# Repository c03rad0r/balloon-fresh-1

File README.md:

# Pico-Balloon Tracker & E80 Range Test Bench

**A pico-balloon relay system: balloons acting as a bent pipe between base stations.**

A flight hub carries a 2.4 GHz FLRC radio, GNSS and a solar harvester, and carries four solar wings. Two
ground base stations reach each other **only through the balloon** — there is no ground-to-ground path.
Each base station has cellular backhaul — LTE Cat 4 (SIM7600E-H), not 5G. See
`docs/TELCO-BACKHAUL-DECISIONS.md` R3: "LTE Cat-4 now. Do NOT buy 5G."

**This README has two parts.** The relay system (below) is the current programme. The E80-STM32 range
test bench further down is the bench instrumentation used to characterise the radio link.

---

## 💬 Discussion & community

Questions, design review and build reports are welcome in the **Pico-Balloon Signal group**:

**https://signal.group/#CJQKIPXPvMIsyJiDb-IwW7FDIM21SUhsRrSs1VqZI30MCaenEhDGbhyyJSvjaXNYMcUDeXGj**

Signal is used deliberately: it needs only a phone number (no email, no account to create) and the
group is end-to-end encrypted, which suits a hardware project where measurements and part choices get
discussed before anything is public. If the invite link has expired, open an issue and ask for a
fresh one.

*New here?* The honest current state of the board — what works, what is open, and what is explicitly
not yet done — is in the **⚠️ Honest state** section just below. Please read it before asking
"is it ready to fly?", because the answer there is kept current and this README is the canonical
place for it.

---

## 🛰 The relay system

### Board status

**Generated** — `docs/boards/GALLERY.md` has renders and a measured table. Regenerate with
`python3 tracker/hardware/make_board_gallery.py`.

| board | footprints | nets routed | tracks | what it is |
|---|---|---|---|---|
| **hub v9** | 59 | **57 / 59** | 834 | flight hub: SX1280 FLRC, GNSS, solar harvester, 4 wing sockets |
| **wing v9** | 15 | **4 / 6** | 20 | wing solar array + cut driver + hub tab |
| **base station** | 44 | **0 / 44** | 0 | ground: SIM7600E-H LTE Cat 4, FLRC to the hub |

Read the `nets routed` column, **not** the amount of copper in a render — a copper pour is not routing.

### Start here by goal

| I want to… | read |
|---|---|
| see the fabrication questions we are asking a fab | [`docs/fab/JLC-QUERY-DRAFT-MESSAGE.md`](docs/fab/JLC-QUERY-DRAFT-MESSAGE.md) |
| see the fab-review reading order | [`docs/fab/README.md`](docs/fab/README.md) |
| see where every gate stands | [`docs/fab/GATE-RESULTS.md`](docs/fab/GATE-RESULTS.md) |
| see what is still missing | [`docs/fab/ASTRA-GAP-ANALYSIS.md`](docs/fab/ASTRA-GAP-ANALYSIS.md) |
| see per-board renders + measured state | [`docs/boards/GALLERY.md`](docs/boards/GALLERY.md) |
| read the wing interface decision record | [`docs/adr/046-wing-board-interface.md`](docs/adr/046-wing-board-interface.md) |

### ⚠️ Honest state

**Fit to show a fabricator for review. Not fit to order.** Open items:

- **`U1.41`** — the radio's exposed ground pad ~~**has no net** (pad-number mismatch)~~ — **CORRECTED
  2026-10-17:** measured, `U1`'s 13 pads numbered `41` are **all on `GND`** (thermal-via array, correct
  by design) and its 9 unnamed pads are `F.Paste`-only stencil apertures. Not a defect. Owning record:
  [`docs/fab/U1-FOOTPRINT-DIAGNOSIS.md`](docs/fab/U1-FOOTPRINT-DIAGNOSIS.md)
- **ERC: 20 errors** — incl. 12 floating `U_CUT1–4` pins; **parity passes**, so the board has not drifted
- **DRC: 16 errors — all 16 are the intentional `J_W*` edge lands. Zero real electrical errors.** The 137
  warnings are silkscreen or library metadata
- **Wing joint geometry is OPEN** (ADR-046 §4.2.1) — so the interface drawing is **held**
- **Base station: 0 of 44 nets routed**, no editable schematic

### Generate the artefacts

```bash
python3 tracker/hardware/make_board_gallery.py      # renders + the measured table
python3 tracker/hardware/make_system_diagram.py     # the diagram above
bash    tracker/hardware/run_erc.sh                 # ERC + schematic-to-board parity
bash    tracker/hardware/fab_grade.sh tracker/hardware/hub_board_v9.kicad_pcb tracker/hardware/output/fabgrade
~/venvs/kicad/bin/python tracker/hardware/tests/test_netlist_integrity.py
```

All three gates are recorded in [`docs/fab/GATE-RESULTS.md`](docs/fab/GATE-RESULTS.md).

### Visual review — how artefacts are checked here

A visual consultant (`gpt-6-astra`) reviews every generated diagram before it is committed:

```bash
python3 tracker/hardware/ask_astra.py --review artefact.png --out review.md
```

**This is not decoration.** It has caught two architecture errors in the system diagram alone — a
one-base-station topology that could not depict a relay, and a wiring path that drew the direct
ground-to-ground link its own label denied. Both survived reading the generator code. See
[`docs/fab/reviews/`](docs/fab/reviews/).

**Regenerate before reviewing.** Reviewing a stale render is reviewing a file that no longer exists.

---

## 🧪 E80-STM32 range test bench

Ultralight (<15 g) pico-balloon tracker (ESP32-C3 + Semtech LR2021) with a
dedicated **E80-STM32 bench firmware** for distributed LoRa/FLRC range
testing.  Two boards, two laptops, one `make` command each — that's all
it takes to run a full PER / RSSI / SNR sweep.

---

## ⚡ Getting Started

```bash
git clone https://github.com/felixfelix-bot/balloon-fresh.git
cd balloon-fresh/firmware/e80-stm32-bench
git checkout feat/2g4-sweep

# One-time: flash the board (needs both USB cables connected)
make flash

# On the TX machine:
make tx

# On the RX machine (within 4 minutes of `make tx`):
make rx

# After both finish, merge logs:
make range-merge RX=rx-log.csv TX=tx-log.csv
```

**That's it.** The system auto-detects serial ports, computes a synchronised
start time (T0), beeps a countdown, and writes results to CSV.

> **Want the minimal package?** Download the pre-built
> [range-test ZIP](../../releases) — contains only the files you need to
> flash + run TX/RX. See [Part 4](#4-minimal-range-test-zip) below.

---

## 📋 Table of Contents

| # | Section |
|---|---------|
| 1 | [What is this repo?](#1-what-is-this-repo) |
| 2 | [Hardware Requirements](#2-hardware-requirements) |
| 3 | [Quick Start (Linux / macOS / Windows)](#3-quick-start) |
| 4 | [Minimal Range-Test ZIP](#4-minimal-range-test-zip) |
| 5 | [Repository Structure](#5-repository-structure) |
| 6 | [Key Documentation](#6-key-documentation) |
| 7 | [Tools Reference](#7-tools-reference) |
| 8 | [Config Presets](#8-config-presets) |
| 9 | [Development & Testing](#9-development--testing) |
| 10 | [Hardware](#10-hardware) |

---

## 1. What is this repo?

This repository hosts **two related projects**:

1. **Pico-Balloon Tracker** — An ESP32-C3 + Semtech LR2021 ultra-light
   balloon tracker (<15 g) with multi-band LoRa (2.4 GHz + Sub-GHz), FLRC
   high-speed mode, 3D PCB-Yagi antenna array, solar/supercap power, and
   BMP280 sensing.

2. **E80 Range Test Bench** — A STM32F103C8T6 based firmware (`firmware/e80-stm32-bench/`)
   for the E80-900MBL-02 board, used for distributed LoRa/FLRC range
   testing.  Measures PER, RSSI, SNR, and bit error rate across modulation
   schemes at various distances.  Two boards act as TX/RX, each connected
   to a separate computer.  Role is set at runtime — boards are
   interchangeable.

---

## 2. Hardware Requirements

| Item | Qty | Notes |
|------|-----|-------|
| E80-900MBL-02 board | 2 | One per machine. Boards are interchangeable (TX/RX is software-selected). |
| Computer (laptop/mini PC) | 2 | One per board. Linux, macOS, or Windows. |
| USB cables | 2 per board | CH340 USB-serial (data) + CMSIS-DAP/Pico SWD probe (debug). Both required. |
| Phone with GPS | 1 (opt.) | For distance measurement. Any app that exports GPX/KML. |

### E80 Board Anatomy

- **STM32F103C8** — microcontroller (64 KB flash / 20 KB RAM)
- **LR2021** — Semtech LoRa Gen 4 radio (supports LoRa + FLRC)
- **CH340** — USB-serial chip for host communication
- **Raspberry Pi Pico** (CMSIS-DAP) — SWD probe for flashing + board reset

### Pico-Balloon Hardware

| Component | Spec |
|-----------|------|
| MCU | ESP32-C3 (ESP-C3-12F / XIAO ESP32C3) |
| LoRa | Semtech LR2021 (Gen 4) / LR1121 (Gen 3 alt.) |
| PA/LNA | Skyworks SKY66112-11 (+22 dBm TX, +14 dB LNA RX) |
| Antennas | 4× PCB-Yagi + SP4T switch (lighthouse mode) |
| Power | 12× solar cells → BAT54 → 2× 3.3 F supercaps → TPS7A02 LDO |
| Sensor | BMP280 (pressure/temperature) |
| Target weight | <15 g |

---

## 3. Quick Start

### Linux

```bash
# Install toolchain
sudo apt install cmake arm-none-eabi-gcc openocd python3 python3-pip
pip install pyserial

# Clone & build
git clone https://github.com/felixfelix-bot/balloon-fresh.git
cd balloon-fresh/firmware/e80-stm32-bench
git checkout feat/2g4-sweep

# Add user to dialout group (needed for serial port access)
sudo usermod -aG dialout "$USER"
# Log out and back in, or: newgrp dialout

# Flash firmware (first time only — both USB cables connected)
make flash
```

### macOS

```bash
# Install toolchain
brew install cmake gcc-arm-embedded openocd python3
pip3 install pyserial

# Clone & build
git clone https://github.com/felixfelix-bot/balloon-fresh.git
cd balloon-fresh/firmware/e80-stm32-bench
git checkout feat/2g4-sweep

make flash
```

### Windows

1. Install [STM32CubeIDE](https://www.st.com/en/development-tools/stm32cubeide.html)
   or a standalone `arm-none-eabi-gcc` toolchain.
2. Install [OpenOCD](https://gnutoolchains.com/arm-eabi/openocd/).
3. Install [Python 3](https://www.python.org/downloads/) + `pip install pyserial`.
4. Clone the repo, open a terminal (Git Bash or PowerShell) in
   `firmware/e80-stm32-bench/`.
5. Run `make flash`.

### Running a Test

```bash
# On TX machine:
make tx

# On RX machine (within 4 minutes of make tx):
make rx

# After both finish (either machine):
make range-merge RX=rx-log.csv TX=tx-log.csv
```

> For full instructions including flashing details, serial port detection,
> GPS stitching, and troubleshooting, see the
> **[E80 Range Test Operator Guide](firmware/e80-stm32-bench/docs/RANGE-TEST-GUIDE.md)**.

---

## 4. Minimal Range-Test ZIP

For operators who just want the files needed to flash + run TX/RX without
cloning the whole repo:

**Download:** See [GitHub Releases](../../releases) for `e80-range-test-*.zip`.

**Build your own:**

```bash
cd firmware/e80-stm32-bench
bash tools/create-range-test-zip.sh
# Output: e80-range-test-<sha7>.zip
```

The ZIP contains:

| Path | Description |
|------|-------------|
| `Makefile` | Convenience targets (flash, tx, rx, merge) |
| `CMakeLists.txt` | Firmware build config |
| `cmake/` | Toolchain file (arm-none-eabi) |
| `ld/` | Linker scripts (STM32F103C8) |
| `src/` | Firmware source code |
| `third_party/` | STM32 HAL + Semtech LR2021 driver |
| `tools/e80_bench_ctl.py` | Board controller — TX/RX, PER bench |
| `tools/e80_detect.py` | Auto-detect board serial port |
| `tools/gps_stitch.py` | Stitch GPS track onto RX packet log |
| `tools/merge_csvs.py` | Merge TX + RX logs into PER report |
| `tools/countdown.py` | Countdown timer with beeps |
| `configs/envelope-4cfg-max.json` | Default range test preset (4 configs, max payload) |
| `configs/outdoor-10.json` | Outdoor range test preset (10 pkts per config) |
| `docs/RANGE-TEST-GUIDE.md` | Full operator guide |
| `README-RANGE-TEST.txt` | Quick start card |

---

## 5. Repository Structure

```
balloon-fresh/
├── firmware/
│   ├── e80-stm32-bench/          # E80 STM32 range test firmware
│   │   ├── Makefile              # Flash, tx, rx, merge targets
│   │   ├── CMakeLists.txt        # Firmware build config
│   │   ├── src/                  # Firmware source (bench, radio, console)
│   │   ├── tools/                # Python tools (comms, GPS, CSV, sweep)
│   │   ├── cmake/                # ARM cross-compile toolchain
│   │   ├── ld/                   # STM32 linker scripts
│   │   ├── third_party/          # STM32 HAL + Semtech LR2021 driver
│   │   ├── docs/                 # RANGE-TEST-GUIDE, flashing, timing analysis
│   │   ├── tests/                # Host-side unit tests (C unit + pytest)
│   │   └── FLASHING.md           # Flashing procedures
│   ├── esp32-c3-flrc/            # ESP32-C3 FLRC bench firmware
│   ├── esp32-bootsel-controller/ # ESP32 boot/select controller
│   ├── esp32-uart-bridge/        # UART bridge firmware
│   ├── rp2040-flrc-max/          # RP2040 FLRC tests
│   └── scripts/                  # Build/deploy scripts
├── mesh-stack/                   # ESP-NOW mesh + FLRC bench + LR2021 drivers
├── hardware/                     # PCB design (KiCad), enclosures
├── configs/                      # Range test config presets (JSON)
├── tools/                        # Shared repo-wide tools & scripts
├── docs/                         # Project documentation, ADRs, plans
├── data/                         # Captured test data & analysis
├── tests/                        # Integration tests
├── bom/                          # Bill of materials
├── ansible/                      # Deployment playbooks (range-setup)
├── scripts/                      # Repo-wide automation scripts
└── tracker/                      # Ground station & tracker firmware
```

---

## 6. Key Documentation

| Document | Description |
|----------|-------------|
| **[Harmonized Cross-Board Bench Package](docs/harmonized/HARMONIZED-BENCH-PACKAGE.md)** | Entry point for cross-board (E80 / ESP32 / RP2040) bench work — real repo URLs and branches, build/flash per family, running a session, handing data back |
| [Harmonized Results](docs/harmonized/HARMONIZED-RESULTS.md) | Results summary by board-pair × band × LEN × BR, with raw CSV links; 868 MHz baseline vs 2.4 GHz semantics |
| [Harmonized Run Report Template](docs/harmonized/HARMONIZED-RUN-REPORT-TEMPLATE.md) | Fill-in template for one harmonized run (identity, provenance, matrix, acceptance, results, anomalies) |
| [Bench Console Spec](docs/BENCH-CONSOLE-SPEC.md) | Normative cross-board console protocol (`ID?/SET/N/PKT/STAT?`, framing, bands) |
| **[E80 Range Test Guide](firmware/e80-stm32-bench/docs/RANGE-TEST-GUIDE.md)** | Complete self-contained operator guide — hardware setup, flashing, TX/RX, merge, GPS, troubleshooting |
| [E80 Flashing Guide](firmware/e80-stm32-bench/FLASHING.md) | Detailed flashing procedures (SWD, stm32flash) |
| [Timing Tolerance Analysis](firmware/e80-stm32-bench/docs/timing-tolerance-analysis.md) | T0 sync mechanism analysis |
| [Hardware Integration Findings](firmware/e80-stm32-bench/docs/hardware-integration-findings.md) | Live hardware test results |
| [Operator Quickstart](firmware/e80-stm32-bench/tools/OPERATOR-QUICKSTART.md) | Quick reference for command structure |
| [ADR Index](docs/adr/) | Architecture Decision Records |
| [Hardware Connections](docs/hardware/HARDWARE_CONNECTIONS.md) | Board wiring reference |

---

## 7. Tools Reference

| Tool | Location | Purpose |
|------|----------|---------|
| `e80_bench_ctl.py` | `firmware/e80-stm32-bench/tools/` | Main board controller — TX burst, RX arm, PER measurement, sweep runner |
| `e80_detect.py` | `firmware/e80-stm32-bench/tools/` | Auto-detect E80 board role + serial port (handles CH340 port swapping) |
| `gps_stitch.py` | `firmware/e80-stm32-bench/tools/` | Stitch GPS track points onto RX packet log by nearest timestamp |
| `merge_csvs.py` | `firmware/e80-stm32-bench/tools/` | Merge TX + RX logs into PER report (joins on session/config/pkt_idx) |
| `countdown.py` | `firmware/e80-stm32-bench/tools/` | Countdown to T0 with terminal bell beeps |
| `e80_sweep_full.py` | `firmware/e80-stm32-bench/tools/` | Full modulation sweep (FLRC + LoRa at multiple bitrates/SF) |
| `create-range-test-zip.sh` | `firmware/e80-stm32-bench/tools/` | Build minimal ZIP package for range test operators |

---

## 8. Config Presets

Config files live in `configs/` at the repo root:

| File | Description |
|------|-------------|
| `outdoor-10.json` | Outdoor range test — 10 pkts per config, 868 MHz EU SRD |
| `indoor-baseline.json` | Indoor baseline test |

Each JSON config specifies a list of modulation configurations:

```json
{
  "label": "FLRC-650 LEN64",
  "mod": "flrc",
  "br": 650,
  "pa": 10,
  "freq": 868000000,
  "plen": 64,
  "gap": 5000,
  "n_pkts": 10
}
```

Fields: `mod` (flrc/lora), `sf` (LoRa spreading factor), `bw` (bandwidth kHz),
`br` (bitrate kbps), `pa` (TX power dBm), `freq` (Hz), `plen` (payload bytes),
`gap` (inter-packet gap ms), `n_pkts` (packets per config).

---

## 9. Development & Testing

```bash
# Firmware build
cd firmware/e80-stm32-bench
make firmware          # Cross-compile with arm-none-eabi-gcc

# Host unit tests (uses system gcc)
make test-host

# Run pytest suite
cd firmware/e80-stm32-bench/tools
python3 -m pytest ../tests/ -v

# Run a dry-run of the range test (prints schedule, no hardware)
make range-dry-run
```

---

## 10. Hardware

| Directory | Description |
|-----------|-------------|
| `hardware/` | PCB design files (KiCad), enclosure CAD |
| `bom/` | Bill of materials |
| `docs/pcb/` | PCB design documentation |
| `docs/hardware-reference/` | Hardware reference materials |

---

## License

See individual source files and `firmware/e80-stm32-bench/third_party/`
for licensing details. Third-party drivers retain their original licenses
(Semtech BSD, ST BSD-3-Clause).

## Cross-Board Bench — dieser Branch (`range-tests`)
Dieser Branch ist die Range-Test-Spur der harmonisierten Cross-Board-Messungen
(E80 STM32+LR2021 / ESP32-C3+LR2021 / RP2040+LR2021). Einstiegspunkt für alles
Weitere ist `docs/harmonized/HARMONIZED-BENCH-PACKAGE.md` im Branch **`main`** desselben
Repos (`https://github.com/felixfelix-bot/balloon-fresh.git`).
> **Wichtig — die Bench-Console liegt NICHT auf diesem Branch.**
> `tools/balloon_sweep.py` und `docs/BENCH-CONSOLE-SPEC.md` gibt es nur auf
> `main` (HARM-Kette, `harm/t5-bench-console`). Auf `range-tests` schlägt
> `ls tools/balloon_sweep.py` fehl. Wer die harmonisierte Console fahren will,
> muss `main` auschecken oder diesen Branch damit mergen; die untenstehenden
> Kommandos sind die *Legacy*-Sweep-Werkzeuge dieses Branches.
### RP2040-Firmware bauen/flashen (dieser Branch)
cd firmware/rp2040
make build-tx        # bzw. build-rx / build-both
make flash-tx        # bzw. flash-rx / flash-both
make monitor-tx      # bzw. monitor-rx
make ports           # Ports neu ermitteln (nicht raten)
### Sweep fahren (Legacy-Weg dieses Branches)
# Board-Mutex ist Pflicht — niemals ohne Lock flashen
BALLOON_TRACK=range-tests python3 ~/repos/balloon-fresh/tools/balloon-board-lock.py \
    acquire board-a --purpose "range sweep" --timeout 120
python3 tools/sweep_flash.py          # flashen
python3 tools/sweep_capture.py 480    # 480 s erfassen (>= 2 Zyklen)
python3 tools/capture_sweep.py        # alternativ: Sweep-Capture
BALLOON_TRACK=range-tests python3 ~/repos/balloon-fresh/tools/balloon-board-lock.py release board-a
Die Ergebnisse und die bekannten Fallstricke dieses Ansatzes (Timing-Drift
zwischen zwei freilaufenden RP2040, Slot-Weiten, IRQ-/RSSI-Opcode-Bugs) stehen in
`docs/bench/SWEEP-RESULTS.md`. Datenübergabe-Konvention dieses Branches:
`docs/data-handover/DATA-HANDOVER-2026-08-17.md`.
### Harmonisierte Session (nur auf `main`)
git checkout main     # Console liegt dort
python3 tools/balloon_sweep.py --tx rp2040 --rx esp32 --session <yymmddHHMM> --dry-run
`REFUSED (pre-hardware, spec enforcement): …` heisst: der Plan verletzt die Spec
(LEN-Cap 255/511, GAP >= 40 000 us bei LEN > 256, Frequenz-Paar). Plan
korrigieren, nicht umgehen. 2.4-GHz-Cross-Board ist nur RP2040<->ESP32 erlaubt.

---

## FIPS over LR2021 / FLRC — reference implementation

A self-contained reference transport lives in
[`reference/fips-lr2021/`](reference/fips-lr2021/README.md).

- native `transports.lr2021` on a pinned FIPS fork (`c03rad0r/fips`, branch
  `balloon-lr2021`), plus a stock-FIPS UDP daemon fallback;
- RP2040 + E80/LR2021 bridge firmware;
- EU 868, US 915 and 2.4 GHz profiles;
- host tests, hardware test scripts and an event runbook.

No PR or issue is opened against `jmcorgan/fips`; the fork tracks upstream and
the event build is pinned by tag `event-2026-11`.

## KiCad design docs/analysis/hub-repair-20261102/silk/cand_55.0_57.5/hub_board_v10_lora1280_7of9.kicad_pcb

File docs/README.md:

# `docs/` — layout

`docs/` was reorganised in three separately-committed stages (branch `pr/repo-cleanup`):
1. **archive** — docs that mark themselves superseded moved to [`archive/`](archive/README.md), each with a header naming its successor.
2. **clusters** — the loose docs at the `docs/` root were filed into the directories below; every referrer was rewritten in the same commit as its move.
3. **contradictions** — see the dated notes in the affected records.

The measurement that made this cheap: of the 277 loose docs, 259 were linked from nowhere, so only ~18 moves needed referrer care.
The per-file inbound count is in [REPO-TRIAGE-INDEX.md](REPO-TRIAGE-INDEX.md) (regenerate with `python3 scripts/repo_triage.py --root docs --out docs`).

## Cluster directories

| directory | what belongs in it | docs moved in |
|---|---|---|
| `docs/balloon/` | pico-balloon scope and test results | 2 |
| `docs/base-station/` | base station, telco backhaul, tollgate decode | 3 |
| `docs/bench/` | bench console, task-chain specs, sweep/throughput results | 17 |
| `docs/design/` | design proposals | 2 |
| `docs/discovery/` | discovery-sync and adoption-roadmap records | 9 |
| `docs/e80-900mbl-02-eval/` | E80 STM32 + 900MBL-02 evaluation (existing home) | 4 |
| `docs/flight/` | flight checklists, bootsel/flashing, firmware prepare lists | 5 |
| `docs/flrc/` | FLRC (SX1280) radio: characterisation, throughput, sweeps, test results | 34 |
| `docs/handovers/` | session / track handover prompts and summaries | 18 |
| `docs/hardware-reference/` | component guides, inventory, wiring, soldering (existing home) | 6 |
| `docs/harmonized/` | harmonised bench runs and results | 4 |
| `docs/link/` | link budget, frequency plan, antenna, regulatory/licence notes | 7 |
| `docs/lr2021/` | LR2021 dual-radio research, SPI/protocol references, bandwidth codes | 15 |
| `docs/nostr/` | Nostr / relay / blossom / meshcore integration notes | 5 |
| `docs/pcb/` | PCB-level design and review (existing home) | 2 |
| `docs/plans/` | plans and proposals (existing home) | 20 |
| `docs/power/` | powerbank and dummy-load work | 2 |
| `docs/prestretch/` | pre-stretching and pressure protocols | 4 |
| `docs/range/` | range / outdoor link tests | 5 |
| `docs/recon/` | reconnaissance / security findings (existing home) | 4 |
| `docs/repo/` | repo-process records: changelog, branch triage, consolidation | 2 |
| `docs/rfa/` | RFA1 / RFA1b / RFA1c modules | 2 |
| `docs/rp2040/` | RP2040 vs ESP32 MCU assessment and bring-up | 8 |
| `docs/sdr/` | SDR tooling and captures | 2 |
| `docs/speed/` | speed-test plans and results | 2 |
| `docs/spi/` | SPI timing and protocol notes | 6 |
| `docs/status/` | point-in-time status reports and audits | 4 |
| `docs/sx1280/` | SX1280 datasheets and references (existing home) | 3 |
| `docs/walk-tests/` | walk-around / walk test procedures and QA | 5 |
| `docs/wing/` | wing structural / electrical / release work | 1 |

## Deliberately left at the `docs/` root

A doc stays at the root when a *machine* reads its path, because moving it would need an edit to the
reader (out of scope for a layout commit). Two kinds:

**Read by code** (tests, tools, generators, firmware config, `.kicad_sch`/`.net`/`.wrl` artifacts):

`2G4-LINK-BUDGET-ANALYSIS.md`, `3d-model-coverage-wing.md`, `ADR-range-sync-cvm.md`, `BALLOON-SWEEP-TOOL.md`, `BASE-STATION-PCBA-D14-FREEZE.md`, `BENCH-CONSOLE-SPEC.md`, `BRANCH-TRIAGE-2026-10-06.md`, `BUILD-SIZE-REPORT.md`, `CHANGELOG.md`, `COEXISTENCE-V9.md`, `DESIGN-contextvm-adaptive.md`, `DUAL-VARIANT-DESIGN.md`, `E80-FLASH-ACCESS-FINDINGS.md`, `E80-PRBS-VERIFY-2026-08-20.md`, `F33-MODULE-PLAN.md`, `FLIGHT-BOARD-AUTO-BOOTSEL.md`, `FLRC-512B-THROUGHPUT-AUDIT-2026-10-06.md`, `FRIDAY-DEMO-CHEATSHEET.md`, `FRIDAY-DEMO-HANDOVER-2026-08-29.md`, `HANDOVER-WING-RELEASE-AND-BYPASS-DIODE.md`, `INTEGRATION-ASSESSMENT.md`, `LINK-BUDGET-LICENCE-EXEMPT.md`, `LR2021-LESSONS-2026-09.md`, `MEASUREMENT-REQUEST-WING-RELEASE.md`, `P4.1-DMA-CHAINING-ZERO-COPY.md`, `PCB-HANDOVER-FOR-JLCPCB.md`, `PLAN-adaptive-sweep-firmware.md`, `PLAN-esp32-vs-rp2040-benchmark.md`, `PLAN-host-driven-bench.md`, `POWER-BUDGET-V9-D2BE.md`, `PRESTRETCH-OVERPRESSURE-INTERLOCK.md`, `RANGE-TEST-PLAN.md`, `RANGE-THROUGHPUT-PLAN.md`, `RF-EXPERIMENT-DESIGN-ANALYSIS.md`, `RFA1-ELRS-LR2021-DIFF-2026-10-12.md`, `RFA1b-FOLLOWUP-650KBPS-ZEROS-2026-10-14.md`, `RFA1b-PRAM-PATCH-VERDICT-2026-10-14.md`, `SECURITY-FINDINGS.md`, `SOFTWARE-PREPARE-LIST.md`, `STATUS-balloon-circuit-design.md`, `STATUS-balloon-nostr.md`, `STATUS-balloon-pow.md`, `STATUS-balloon-pre-stretching.md`, `STATUS-balloon-range-tests.md`, `STATUS-balloon-speed-tests.md`, `STATUS-balloon-tollgate.md`, `balloon-flight-lessons.md`, `balloon-options-analysis.md`, `balloon-pressure-test.md`, `balloon-test-results.md`, `blossom-design.md`, `bw-code-table.md`, `flrc-rx-verified-results-2026-07-16.md`, `guard-time-config-cvm-optimization-plan.md`, `inventory.md`, `lr2021-flrc-24ghz-datasheet-audit-2026-07-26.md`, `lr2021-spi-command-reference.md`, `lr2021-spi-protocol-reference.md`, `plan.md`, `power-sweep-results-2026-07-24.md`, `rca-fix-plan-20260821.md`, `uart-bridge-pin-verification.md`, `uart-telemetry-protocol.md`

**Read by the SSOT registry / generated** (edit `docs/ssot/parameters.json` first if these ever move):

- `v9-BOM.md` — generated by `scripts/gen_v9_bom.py` (fixed output path).
- `V9-RADIO-SITE-MATRIX.md`, `WING-TO-HUB-SOCKET-SPEC.md`, `hardware-design.md` — `scan[]`/`anchor` paths in `docs/ssot/parameters.json`.
- `REPO-TRIAGE-INDEX.md` / `.json` — generated by `scripts/repo_triage.py`.

Nothing was deleted: the `.md` count is preserved (base 683 + the generated index + the READMEs added here).

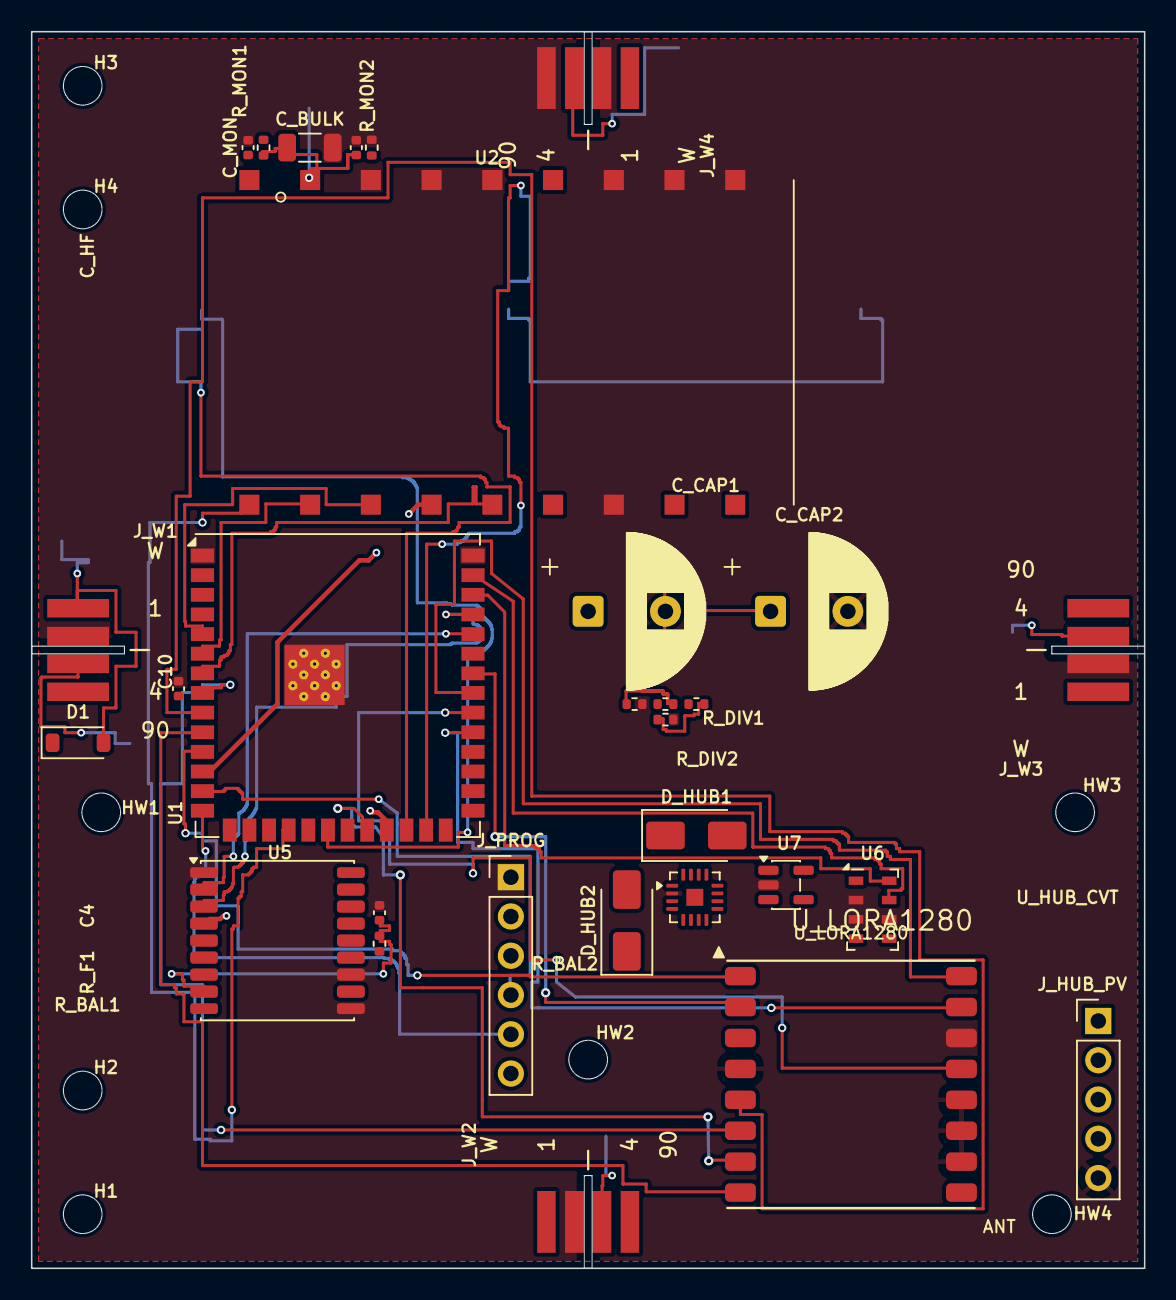
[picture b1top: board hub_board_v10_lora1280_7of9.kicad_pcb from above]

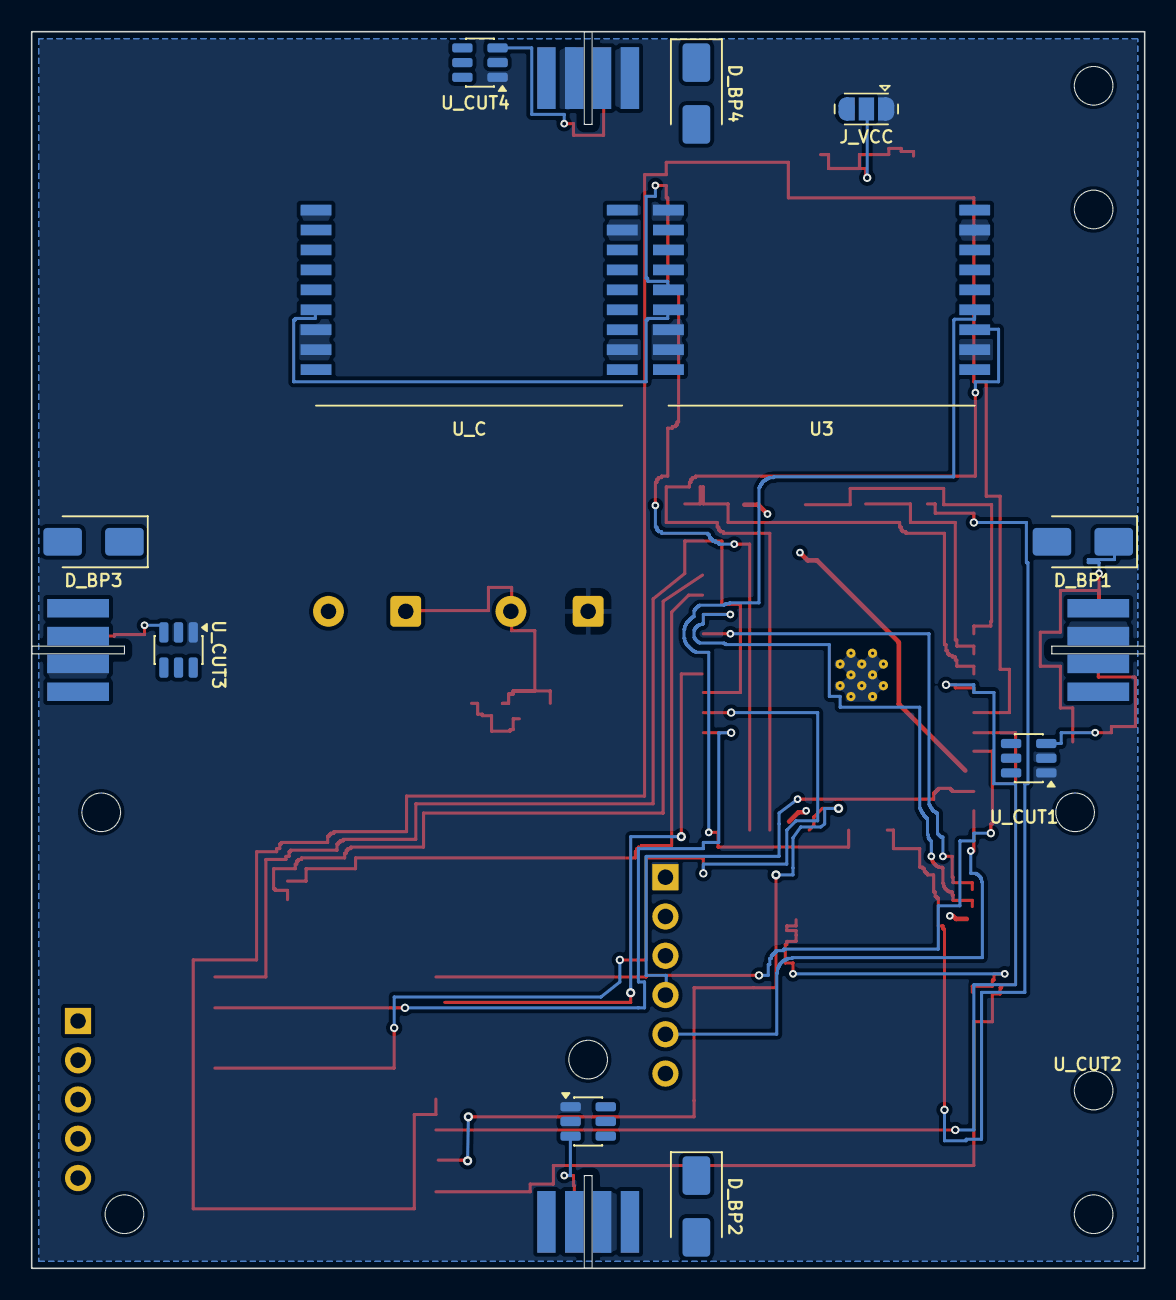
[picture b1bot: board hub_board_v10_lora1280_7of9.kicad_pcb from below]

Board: 4 copper layers, 72.0 x 80.0 mm, 49 parts (11 on the bottom side), 48 nets.

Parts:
C4, C10: 10uF; C_0402_1005Metric
C_BULK: 100uF; C_1206_3216Metric
C_CAP1: C_CAP1; CP_Radial_D10.0mm_P5.00mm
C_CAP2: C_CAP2; CP_Radial_D10.0mm_P5.00mm
C_HF: 100nF; C_0402_1005Metric
C_MON: 10nF; C_0402_1005Metric
D1: BAT54; D_SOD-123
D_BP1, D_BP2, D_BP3, D_BP4: SS24; D_SMA
D_HUB1, D_HUB2: SS24; D_SMA
H1, H2, H3, H4: TETHER_NPTH_D2.5; MountingHole_2.5mm
HW1, HW2, HW3, HW4: STRING_NPTH_D2.5; MountingHole_2.5mm
J_HUB_PV: HUB_PV_PANEL_5P (P | MID1 | spare | N | GND); PinHeader_1x05_P2.54mm_Vertical
J_PROG: J_PROG; PinHeader_1x06_P2.54mm_Vertical
J_VCC: F33_VCC_SEL (VSCAP | +3V3); SolderJumper-3_P1.3mm_Open_RoundedPad1.0x1.5mm
J_W1, J_W2, J_W3, J_W4: WING_SOCKET_4P; Wing_Tab_4P
R_BAL1, R_BAL2: 10k; R_0402_1005Metric
R_DIV1, R_DIV2: 1M; R_0402_1005Metric
R_F1: 100R; R_0402_1005Metric
R_MON1, R_MON2: 4.7M; R_0402_1005Metric
U1: U1; ESP32-S3-WROOM-1U
U2: U2; LoRa2021F33_2G4
U3: U3; LoRa2021_Castellated
U5: U5; ublox_MAX
U6: U6; LGA-8_3x5mm_P1.25mm
U7: U7; SOT-23-5
U_C: U_C; LoRa2021_Castellated
U_CUT1, U_CUT2, U_CUT3, U_CUT4: latched cut driver + cut-sense (part TODO(unverif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; SOT-23-6
U_HUB_CVT: U_HUB_CVT; VQFN-16-1EP_3x3mm_P0.5mm_EP1.1x1.1mm
U_LORA1280: LoRa1280

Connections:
+3V3: C10.1, J_PROG.2, J_VCC.3, R_F1.1, U1.2, U2.5, U3.1, U5.6, U5.7, U5.9, U6.1, U6.4, U6.5, U7.5, U_C.1, U_LORA1280.3 (VCC)
/CUT_SENSE_W1: J_W1.3, U_CUT1.3
/CUT_SENSE_W2: J_W2.3, U_CUT2.3
/CUT_SENSE_W3: J_W3.3, U_CUT3.3
/CUT_SENSE_W4: J_W4.3, U_CUT4.3
/E28_BUSY: U1.31, U_LORA1280.15 (BUSY)
/E28_CS_N: U1.10, U_LORA1280.8 (NSS)
/E28_DIO1: U1.33, U_LORA1280.16 (DIO1)
/E28_DIO2: U1.11, U_LORA1280.1 (DIO2)
/E28_DIO3: U1.34, U_LORA1280.2 (DIO3)
/E28_RESET_N: U1.32, U_LORA1280.13 (NRESET)
/EN: J_PROG.3, U1.3
/F33_BUSY: U1.12, U2.14
/F33_CS_N: U1.7, U2.13
/F33_IRQ: U1.17, U2.18
/F33_RESET_N: U1.18, U2.17
/F33_VCC: C_BULK.1, C_HF.1, J_VCC.2, R_MON1.1, U2.1
/F33_VSENSE: C_MON.1, R_MON1.2, R_MON2.1, U1.21
/GNSS_PPS: U1.23, U5.4
/GNSS_RX: U1.37, U5.3
/GNSS_TX: U1.36, U5.2
/GNSS_VCC: C4.1, R_F1.2, U5.8
/HUB_PV_MID1: D_HUB1.2, D_HUB2.1, J_HUB_PV.2
/HUB_PV_N: D_HUB2.2, J_HUB_PV.4, U_HUB_CVT.3
/HUB_PV_P: D_HUB1.1, J_HUB_PV.1, U_HUB_CVT.1
/I2C_SCL: U1.38, U6.8
/I2C_SDA: U1.39, U6.7
/SCAP_ADC: R_DIV1.2, R_DIV2.1
/SCAP_MID: C_CAP1.2, C_CAP2.1, R_BAL1.2, R_BAL2.1
/SPI1_MISO: U1.9, U3.3, U_C.3, U_LORA1280.5 (MISO)
/SPI1_MOSI: U1.8, U3.4, U_C.4, U_LORA1280.6 (MOSI)
/SPI1_SCK: U1.22, U3.5, U_C.5, U_LORA1280.7 (SCK)
/SPI2_MISO: U1.6, U2.16
/SPI2_MOSI: U1.5, U2.15
/SPI2_SCK: U1.4, U2.12
/U3_BUSY: U1.24, U3.7
/U3_CS_N: U1.20, U3.6
/U3_IRQ: U1.19, U3.15
/U3_RESET_N: U1.25, U3.14
/USB_DN: J_PROG.4, U1.13
/USB_DP: J_PROG.5, U1.14
/VSCAP: C_CAP1.1, D1.1, J_VCC.1, R_BAL1.1, R_DIV1.1, U7.1, U7.3, U_CUT1.1, U_CUT2.1, U_CUT3.1, U_CUT4.1
/VTCXO_VNTC: U3.13, U_C.13
/W1_SOLAR_N: D_BP1.2, D_BP2.1, J_W1.4, J_W2.1
/W1_SOLAR_P: D1.2, D_BP1.1, J_W1.1
/W2_SOLAR_N: D_BP2.2, D_BP3.1, J_W2.4, J_W3.1
/W3_SOLAR_N: D_BP3.2, D_BP4.1, J_W3.4, J_W4.1
GND: C4.2, C10.2, C_BULK.2, C_CAP2.2, C_HF.2, C_MON.2, D_BP4.2, J_HUB_PV.5, J_PROG.1, J_W1.2, J_W2.2, J_W3.2, J_W4.2, J_W4.4, R_BAL2.2, R_DIV2.2, R_MON2.2, U1.1, U1.40, U1.41, U2.2, U2.3, U2.4, U2.6, U2.7, U2.8, U2.11, U3.2, U3.8, U3.11, U3.12, U3.18, U5.1, U5.10, U5.12, U6.2, U6.3, U6.6, U7.2, U_C.2, U_C.8, U_C.11, U_C.12, U_C.18, U_CUT1.2, U_CUT2.2, U_CUT3.2, U_CUT4.2, U_HUB_CVT.2, U_LORA1280.4 (GND), U_LORA1280.10 (GND), U_LORA1280.11 (GND), U_LORA1280.12 (GND), U_LORA1280.14 (GND)
